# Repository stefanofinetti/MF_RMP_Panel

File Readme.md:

# Radio Management Panel (RMP)

An Airbus A319/320/321 Radio Management Panel for MobiFlight: a 3D-printed
front panel, keys and case, four boards, and two 6-digit frequency displays.
It runs on the **stock MobiFlight Mega firmware**: no custom firmware to
build or flash.

## V5 in short

V5 replaces the earlier version of this repository, a single board with
OLED displays and its own firmware. It is a new design:

* **four boards** instead of one: the logic, the keys and display drivers,
  the lighting, and a carrier for each frequency display;
* **7-segment displays** driven by two MAX7219, which MobiFlight drives
  natively as one LED module;
* **stock firmware**, MobiFlight Mega, core 3.1.4;
* the printed parts are drawn in **FreeCAD 1.1**.

**Status (October 2026):** the unit is built and in use. The boards in this
repository are the built ones, with one correction on the MainPanel (see
[Known issues](#known-issues)). All four are in KiCad 10, with ERC, DRC and
schematic parity clean. The printed parts are being reorganised.

## What is in the repository

| Folder | What it holds |
|---|---|
| [`BoardPanel/`](BoardPanel/README.md) | The logic board: ATmega2560, CH340G USB, 12 V and 5 V supply |
| [`MainPanel/`](MainPanel/README.md) | The keys, the two MAX7219, and the connectors to every other board |
| [`LedsPanel/`](LedsPanel/README.md) | The backlight and the thirteen key lights |
| [`7Segments/`](7Segments/README.md) | The carrier of one frequency display. Two are needed |
| `Libraries/` | The parts shared by the four boards: `RMP.kicad_sym`, `RMP.pretty` and the vendor 3D models in `3dmodels/` |
| `SF_RMP/` | `SF RMP.mfmc`, the MobiFlight board config |
| `3D FIles/` | The FreeCAD sources (`RMP_Panel.FCStd` is the whole assembly), the STL files, the B612 fonts of the legends. Being reorganised |

## The boards

```
 12 V jack ─► BoardPanel ─┬─ J4 ribbon ─► MainPanel J2 ─► J1 ─► LedsPanel (plugged in)
 USB-B     ─►             ├─ J5 ribbon ─► MainPanel J3   keys, encoders, ON/OFF
                          └─ J3 ribbon ─► MainPanel J9 ─┬─ J7 ribbon ─► 7Segments ACTIVE
                                                        └─ J8 ribbon ─► 7Segments STBY
```

| Board | PCB (mm) | What is on it |
|---|---|---|
| [BoardPanel](BoardPanel/README.md) | 110 × 55 | ATmega2560, CH340G, USB-B, 12 V jack, P78A05 5 V module, ISP header |
| [MainPanel](MainPanel/README.md) | 122 × 80 | 13 keys, 2 × MAX7219, encoder and switch connectors |
| [LedsPanel](LedsPanel/README.md) | 122 × 80 | 69 backlight LEDs with their PWM switch, 13 key lights |
| [7Segments](7Segments/README.md) × 2 | 51 × 20 | Two 3-digit common-cathode displays, MHz and kHz |

All four are two-layer, 1.6 mm boards, sized for hand soldering, with
values, polarity and pin 1 on the silkscreen.

## Building one

1. **Print** the panel, keys, case and supports from `3D FIles/`.
2. **Order the boards.** Run the Fabrication Toolkit plugin in each KiCad
   project for the Gerbers, BOM and positions. Order the 7Segments twice.
3. **Assemble** them. The board readmes list what to watch for.
4. **Cable them** as in the diagram above: straight ribbons, pin 1 to
   pin 1. The LedsPanel plugs straight into the MainPanel's J1.
5. **Burn the bootloader** once through the ISP header J2 of the BoardPanel,
   with JP1 on 2–3; then put JP1 back on 1–2. See the
   [BoardPanel readme](BoardPanel/README.md#burning-the-bootloader).
6. **Flash the MobiFlight Mega firmware** from the MobiFlight Connector,
   then load `SF_RMP/SF RMP.mfmc` and upload it to the board.
7. **Bind** the keys, lights, displays and encoders in your MobiFlight
   project.

The BoardPanel's logic runs from USB; the 12 V adapter feeds the backlight,
the displays and the fan.

## MobiFlight

Stock **MobiFlight Mega** firmware, module name `SF RMP`. The config in
`SF_RMP/SF RMP.mfmc` holds:

| Device | Type | Pins |
|---|---|---|
| `Display Freq` | LED module, MAX7219, 2 devices | DIN D23, CLK D22, CS D68. Connector 1 = STBY, connector 2 = ACTIVE |
| `Dimmer` | Output, PWM | D6, the backlight |
| `KHZ_Encoder` | Encoder | Left D27, right D25 |
| `MHZ_Encoder` | Encoder | Left D28, right D26 |
| `VHF1_LED` … `SEL_LED` | Outputs | A0–A12 (D54–D66): VHF1, VHF2, VHF3, HF1, HF2, AM, NAV, VOR, ILS, MLS, ADF, BFO, SEL |

| Key | Pin | Key | Pin | Key | Pin |
|---|---|---|---|---|---|
| XFER | D29 | HF2 | D36 | MLS | D31 |
| VHF1 | D39 | AM | D35 | ADF | D30 |
| VHF2 | D15 | NAV | D34 | BFO | D40 |
| VHF3 | D14 | VOR | D33 | ON/OFF | D41 |
| HF1 | D37 | ILS | D32 | | |

Each MAX7219 drives six digits; the decimal point after the MHz is set in
the project row of each display.

## Known issues

* **The first MainPanel had the two MAX7219 side by side instead of in a
  chain.** The files here are corrected. A board built from the first files
  needs two wires, described in the
  [MainPanel readme](MainPanel/README.md#boards-built-before-this-revision).
* **Two STL files are empty:** the white parts of the VHF1 and VHF3 keys.
  They will be re-exported from FreeCAD with the reorganisation of the
  printed parts.

## Software

* [KiCad](https://www.kicad.org/) 10. The files are saved by KiCad 10 and
  do not open in older versions
* [FreeCAD](https://www.freecad.org/) 1.1, to change the printed parts
* [MobiFlight](https://www.mobiflight.com/)

```bash
git clone https://github.com/stefanofinetti/MF_RMP_Panel.git
```

## License

This code and all the items are released under the GPLv3.0 license. Feel free
to use them as you wish, as long as you redistribute the source code.
A mention would be nice, though, if you use this work: I invested a good
many hours in it, just for the amazing MobiFlight community.

## Acknowledgements

This project couldn't have seen the light without the excellent work, and
kind support, of [GaGagu](https://github.com/gagagu) and
[ElRal](https://github.com/elral). Their work is amazing, so please have a
look at their repositories.

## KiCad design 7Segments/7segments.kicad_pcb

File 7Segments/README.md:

# RMP 7Segments

The carrier of one frequency display: two 3-digit 7-segment displays,
MHz and kHz, side by side. **Two are needed**, one for ACTIVE and one for
STBY. Each sits in its printed display case and reaches the MainPanel
through a 16-pin ribbon.

* **PCB:** 51 × 20 mm, 2 layers, 1.6 mm, GND poured on both sides.
* **Fixing:** six M2 holes.
* **Parts:** 5: four socket strips for the displays on the top, one header
  on the bottom.
* **Status:** built and in use. ERC and schematic parity are clean; DRC
  reports only silkscreen clipped by the solder mask around J5.

| Top: the display sockets | Bottom: J5 |
|---|---|
|  |  |

Rendered by KiCad from the board file. The bottom is seen from below, so it
is mirrored against the top.

## Connectors

| Ref | What | Notes |
|---|---|---|
| J1 / J2 | Socket strips 1 × 6 / 1 × 5 | kHz display, upper and lower row of pins |
| J3 / J4 | Socket strips 1 × 6 / 1 × 5 | MHz display, upper and lower row of pins |
| J5 | Shrouded IDC header 2 × 8, on the bottom | To MainPanel J7 (ACTIVE) or J8 (STBY), pin 1 to pin 1 |

**J5:** odd pins are the segments, 1 A, 3 B, 5 C, 7 D, 9 E, 11 F, 13 G,
15 the decimal point; even pins are the digits, 2 / 4 / 6 kHz 3 / 2 / 1,
8 / 10 / 12 MHz 3 / 2 / 1; 14 and 16 GND.

The displays must be **common cathode**: the MAX7219 sinks the digits and
drives the segments. The decimal point is wired on both displays; which digit
shows it is set in the MobiFlight project.

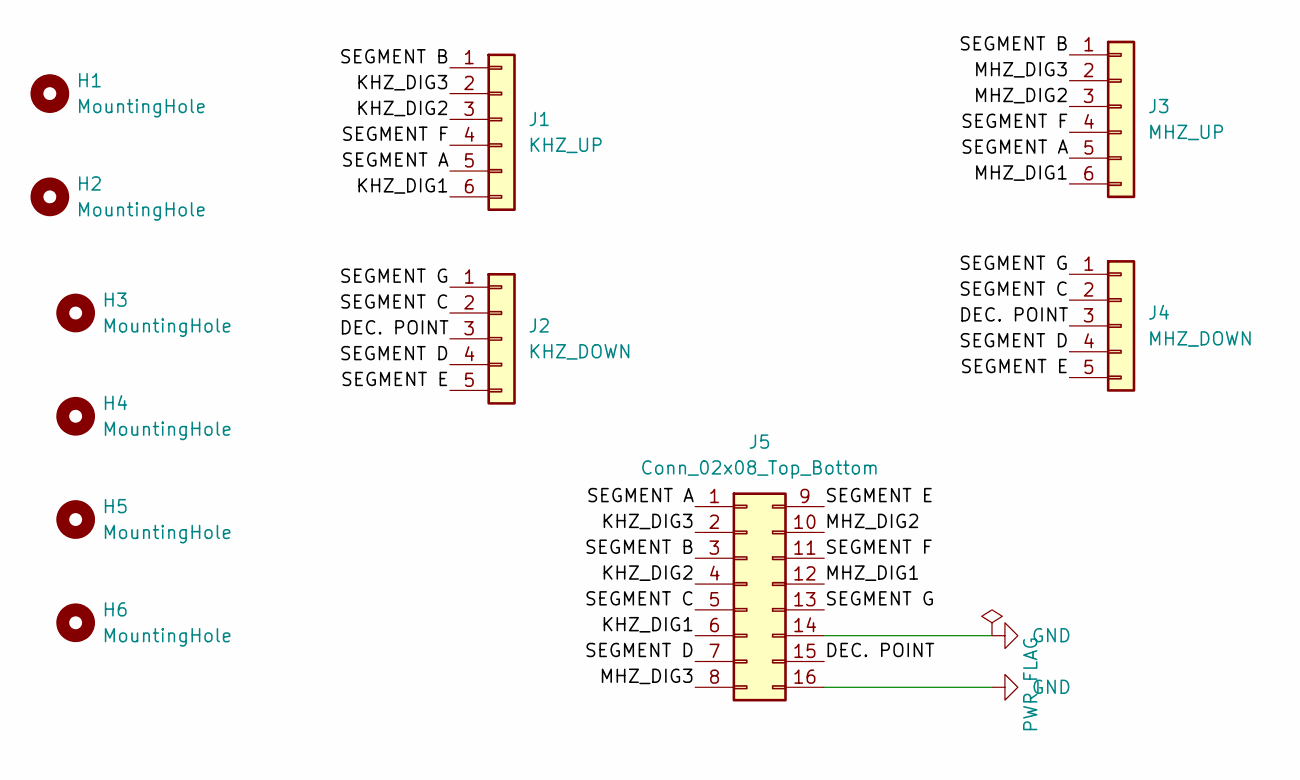
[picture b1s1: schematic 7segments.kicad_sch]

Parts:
H1, H2, H3, H4, H5, H6: MountingHole; MountingHole_2.2mm_M2
J1: KHZ_UP; PinSocket_1x06_P2.54mm_Vertical
J2: KHZ_DOWN; PinSocket_1x05_P2.54mm_Vertical
J3: MHZ_UP; PinSocket_1x06_P2.54mm_Vertical
J4: MHZ_DOWN; PinSocket_1x05_P2.54mm_Vertical
J5: Conn_02x08_Top_Bottom; IDC-Header_2x08_P2.54mm_Vertical

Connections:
/DEC. POINT: J2.3, J4.3, J5.15
/KHZ_DIG1: J1.6, J5.6
/KHZ_DIG2: J1.3, J5.4
/KHZ_DIG3: J1.2, J5.2
/MHZ_DIG1: J3.6, J5.12
/MHZ_DIG2: J3.3, J5.10
/MHZ_DIG3: J3.2, J5.8
/SEGMENT A: J1.5, J3.5, J5.1
/SEGMENT B: J1.1, J3.1, J5.3
/SEGMENT C: J2.2, J4.2, J5.5
/SEGMENT D: J2.4, J4.4, J5.7
/SEGMENT E: J2.5, J4.5, J5.9
/SEGMENT F: J1.4, J3.4, J5.11
/SEGMENT G: J2.1, J4.1, J5.13
GND: J5.14, J5.16

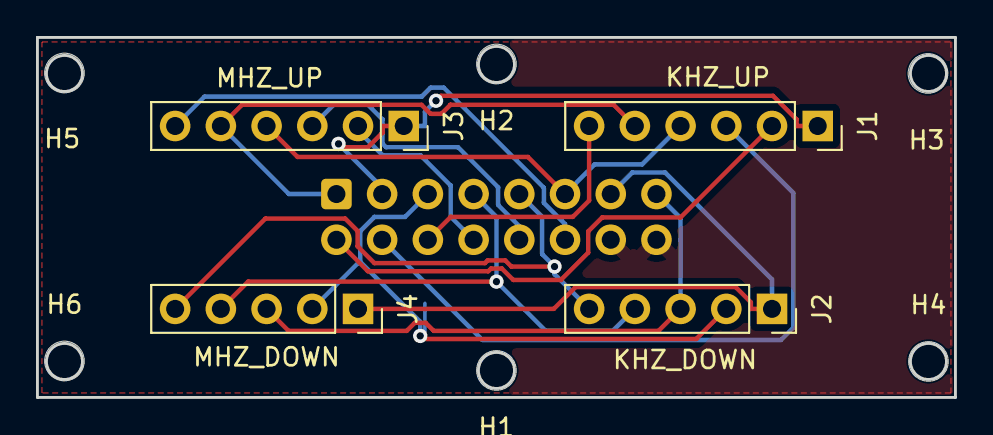
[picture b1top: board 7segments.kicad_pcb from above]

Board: 2 copper layers, 51.0 x 20.0 mm, 11 parts (1 on the bottom side), 15 nets.

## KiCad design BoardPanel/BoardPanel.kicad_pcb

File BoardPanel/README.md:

# RMP BoardPanel

The logic board of the RMP: the microcontroller, USB and power. It stands
upright on the printed support at the back of the case and reaches the
MainPanel through three ribbons.

* **PCB:** 110 × 55 mm, 2 layers, 1.6 mm, GND poured on both sides.
* **Fixing:** six M2 holes.
* **Parts:** 44, all on the top.
* **Status:** built and in use. ERC, DRC and schematic parity are clean.

| Top | Bottom |
|---|---|
|  |  |

Rendered by KiCad from the board file. The bottom is seen from below, so it
is mirrored against the top.

## What is on it

* **Microcontroller:** ATmega2560 (U1) with a 16 MHz crystal, and a CH340G
  (U3, 12 MHz crystal) for USB. MobiFlight sees it as a Mega.
* **Power:**
  * 12 V from the barrel jack J1, through D2, is the `+12V` rail: the
    backlight (J4) and the fan (J6).
  * From `+12V`, through D1, a P78A05 switching module (U2) makes the 5 V
    for the two MAX7219 only (J3).
  * The ATmega and the CH340G run from USB, through D3 and JP1. The
    displays and the backlight need the 12 V; the logic does not.

## Connectors and settings

| Ref | What | Notes |
|---|---|---|
| J1 | 12 V in, 5.5 × 2.1 barrel jack | Pin 1 `+`, through D2 |
| P1 | USB-B | To the computer |
| J2 | ISP header, 1 × 6 | 1 VCC, 2 RESET, 3 MISO, 4 MOSI, 5 SCK, 6 GND |
| JP1 | Power selector | 1–2: MCU from USB (normal use). 2–3: MCU from J2's VCC only, to burn the bootloader |
| J3 | Displays, IDC 2 × 3 | To MainPanel J9 |
| J4 | LEDs and backlight, IDC 2 × 9 | To MainPanel J2 |
| J5 | Buttons and encoders, IDC 2 × 11 | To MainPanel J3 |
| J6 | Cooling fan, 2 pins | `+12V` and GND, for a 12 V fan |
| S1 | Reset | |

Every ribbon is straight, pin 1 to pin 1.

**J3, displays:** 1 `+5V`, 2 GND, 3 D67 (marked `AL`, no longer used, see
the MainPanel), 4 CLK (D22), 5 DIN (D23), 6 LOAD (D68).

**J4, LEDs and backlight:** 1 `+12V`, 2 GND, 3 backlight PWM (D6), 4 GND,
5–17 the thirteen key LEDs (A0–A12, in the order VHF1, VHF2, VHF3, HF1,
HF2, AM, NAV, VOR, ILS, MLS, ADF, BFO, SEL), 18 GND.

**J5, buttons and encoders:** see the pin map in the
[main readme](../Readme.md#mobiflight).

## Burning the bootloader

A new ATmega2560 is blank. Put JP1 on 2–3, so the programmer powers the
MCU alone through J2, and burn the Arduino Mega bootloader once. Then put
JP1 back on 1–2. From then on the board is flashed over USB like a Mega.

## Assembly notes

* Everything is sized for hand soldering: 1206 passives, 5 × 3.2 mm
  crystals.
* Values, polarity and pin 1 are on the silkscreen.

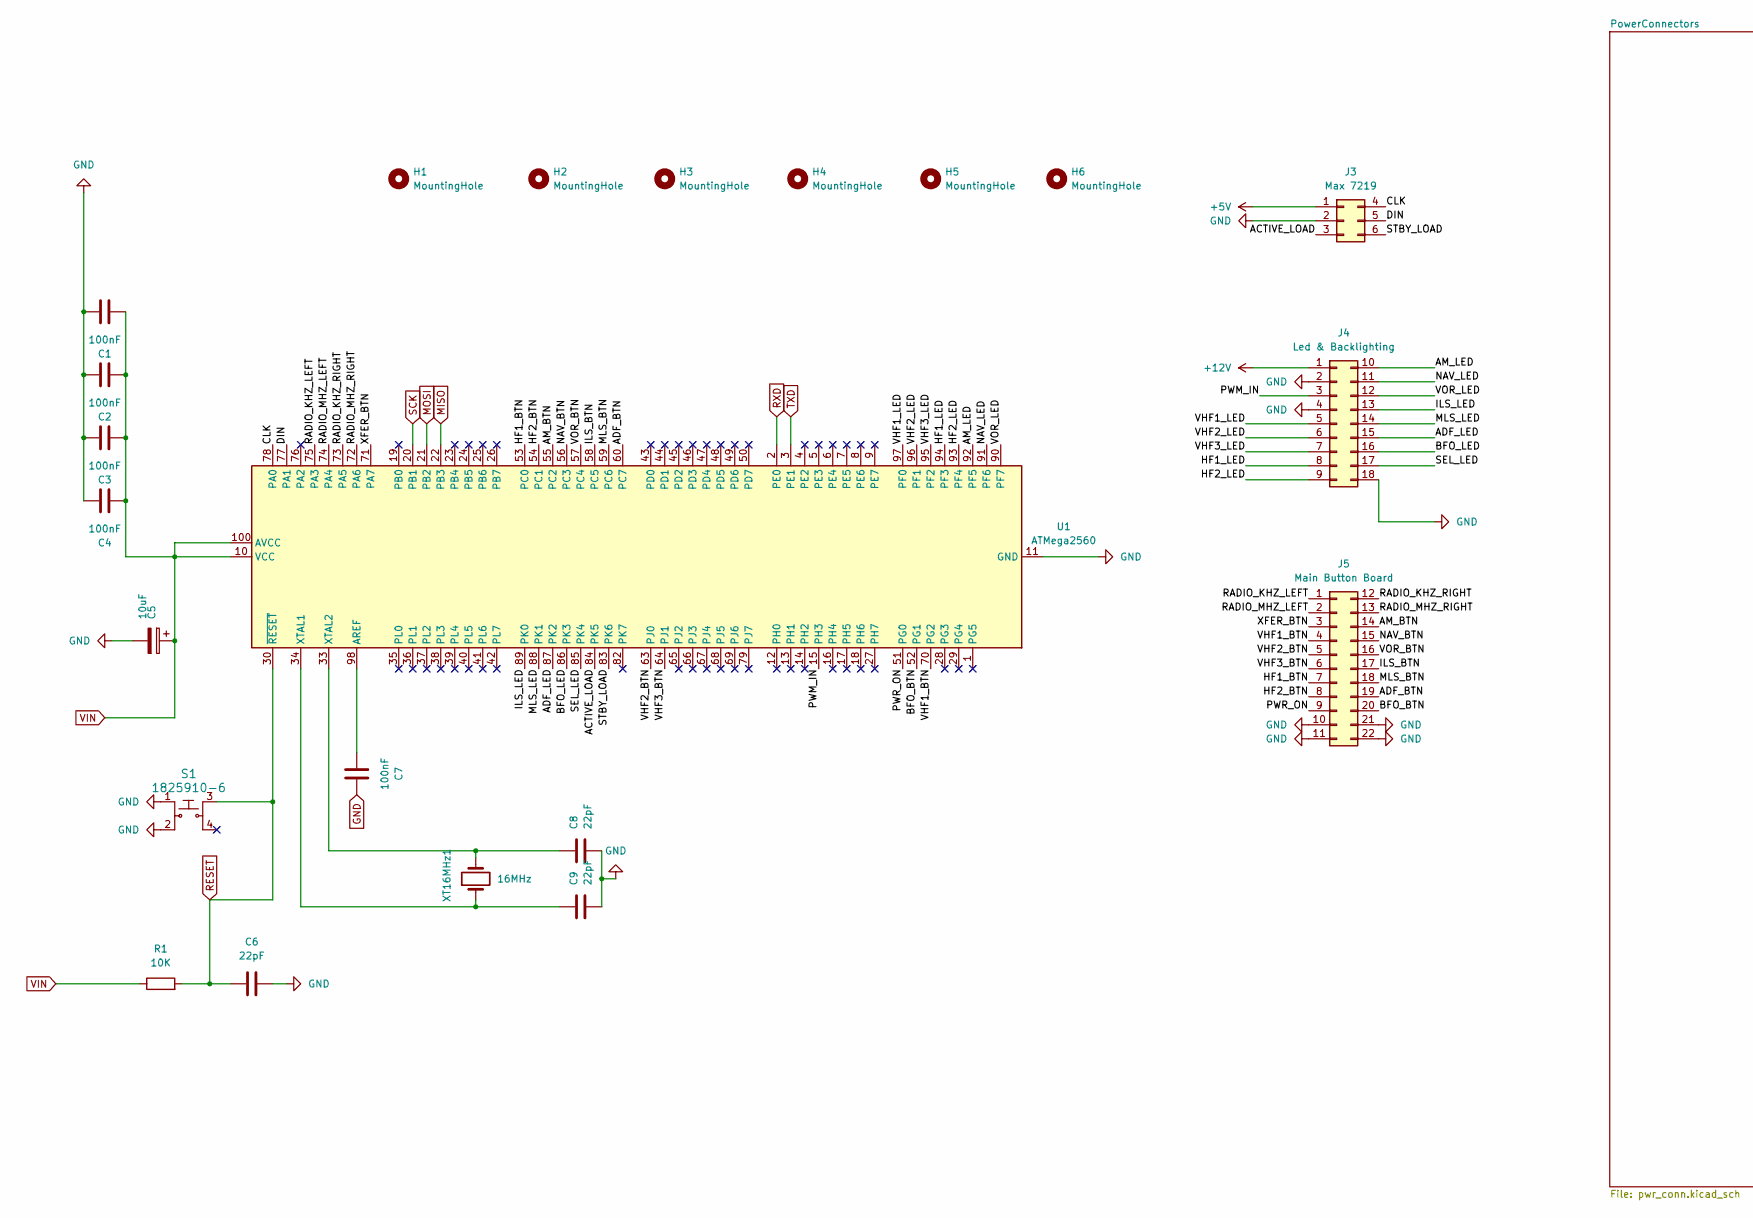
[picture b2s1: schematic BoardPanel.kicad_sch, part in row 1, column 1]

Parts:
C1, C2, C3, C4, C7: 100nF; C_1206_3216Metric_Pad1.33x1.80mm_HandSolder
C5: 10uF; C_Elec_4x5.4
C6, C8, C9: 22pF; C_1206_3216Metric_Pad1.33x1.80mm_HandSolder
H1, H2, H3, H4, H5, H6: MountingHole; MountingHole_2.2mm_M2_DIN965
J3: Max 7219; IDC-Header_2x03_P2.54mm_Vertical
J4: Led & Backlighting; IDC-Header_2x09_P2.54mm_Vertical
J5: Main Button Board; IDC-Header_2x11_P2.54mm_Vertical
R1: 10K; R_1206_3216Metric_Pad1.30x1.75mm_HandSolder
S1: 1825910-6; Switch_Tactile_THT_6x6mm_MJTP1230; MPN 1825910-6; Digi-Key_PN 450-1650-ND
U1: ATMega2560; TQFP100-0.5-14X14MM
XT16MHz1: 16MHz; Crystal_SMD_5032-2Pin_5.0x3.2mm_HandSoldering

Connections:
+5V: J3.1; also elsewhere on the board
+12V: J4.1; also elsewhere on the board
/ACTIVE_LOAD: J3.3, U1.84 (PK5)
/ADF_BTN: J5.19, U1.60 (PC7)
/ADF_LED: J4.15, U1.87 (PK2)
/AM_BTN: J5.14, U1.55 (PC2)
/AM_LED: J4.10, U1.92 (PF5)
/BFO_BTN: J5.20, U1.52 (PG1)
/BFO_LED: J4.16, U1.86 (PK3)
/CLK: J3.4, U1.78 (PA0)
/DIN: J3.5, U1.77 (PA1)
/HF1_BTN: J5.7, U1.53 (PC0)
/HF1_LED: J4.8, U1.94 (PF3)
/HF2_BTN: J5.8, U1.54 (PC1)
/HF2_LED: J4.9, U1.93 (PF4)
/ILS_BTN: J5.17, U1.58 (PC5)
/ILS_LED: J4.13, U1.89 (PK0)
/MLS_BTN: J5.18, U1.59 (PC6)
/MLS_LED: J4.14, U1.88 (PK1)
/NAV_BTN: J5.15, U1.56 (PC3)
/NAV_LED: J4.11, U1.91 (PF6)
/PWM_IN: J4.3, U1.15 (PH3)
/PWR_ON: J5.9, U1.51 (PG0)
/RADIO_KHZ_LEFT: J5.1, U1.75 (PA3)
/RADIO_KHZ_RIGHT: J5.12, U1.73 (PA5)
/RADIO_MHZ_LEFT: J5.2, U1.74 (PA4)
/RADIO_MHZ_RIGHT: J5.13, U1.72 (PA6)
/SEL_LED: J4.17, U1.85 (PK4)
/STBY_LOAD: J3.6, U1.83 (PK6)
/VHF1_BTN: J5.4, U1.70 (PG2)
/VHF1_LED: J4.5, U1.97 (PF0)
/VHF2_BTN: J5.5, U1.63 (PJ0)
/VHF2_LED: J4.6, U1.96 (PF1)
/VHF3_BTN: J5.6, U1.64 (PJ1)
/VHF3_LED: J4.7, U1.95 (PF2)
/VOR_BTN: J5.16, U1.57 (PC4)
/VOR_LED: J4.12, U1.90 (PF7)
/XFER_BTN: J5.3, U1.71 (PA7)
GND: C1.2, C2.2, C3.2, C4.2, C5.2, C6.2, C7.2, C8.2, C9.2, J3.2, J4.2, J4.4, J4.18, J5.10, J5.11, J5.21, J5.22, S1.1, S1.2, U1.11 (GND), U1.32 (GND), U1.62 (GND), U1.81 (GND), U1.99 (GND); also elsewhere on the board
MISO: U1.22 (PB3); also elsewhere on the board
MOSI: U1.21 (PB2); also elsewhere on the board
unnamed: C7.1, U1.98 (AREF)
unnamed: C9.1, U1.34 (XTAL1), XT16MHz1.1
unnamed: C8.1, U1.33 (XTAL2), XT16MHz1.2
RESET: C6.1, R1.2, S1.3, U1.30 (~RESET); also elsewhere on the board
RXD: U1.2 (PE0); also elsewhere on the board
SCK: U1.20 (PB1); also elsewhere on the board
TXD: U1.3 (PE1); also elsewhere on the board
VIN: C1.1, C2.1, C3.1, C4.1, C5.1, R1.1, U1.10 (VCC), U1.31 (VCC), U1.61 (VCC), U1.80 (VCC), U1.100 (AVCC); also elsewhere on the board

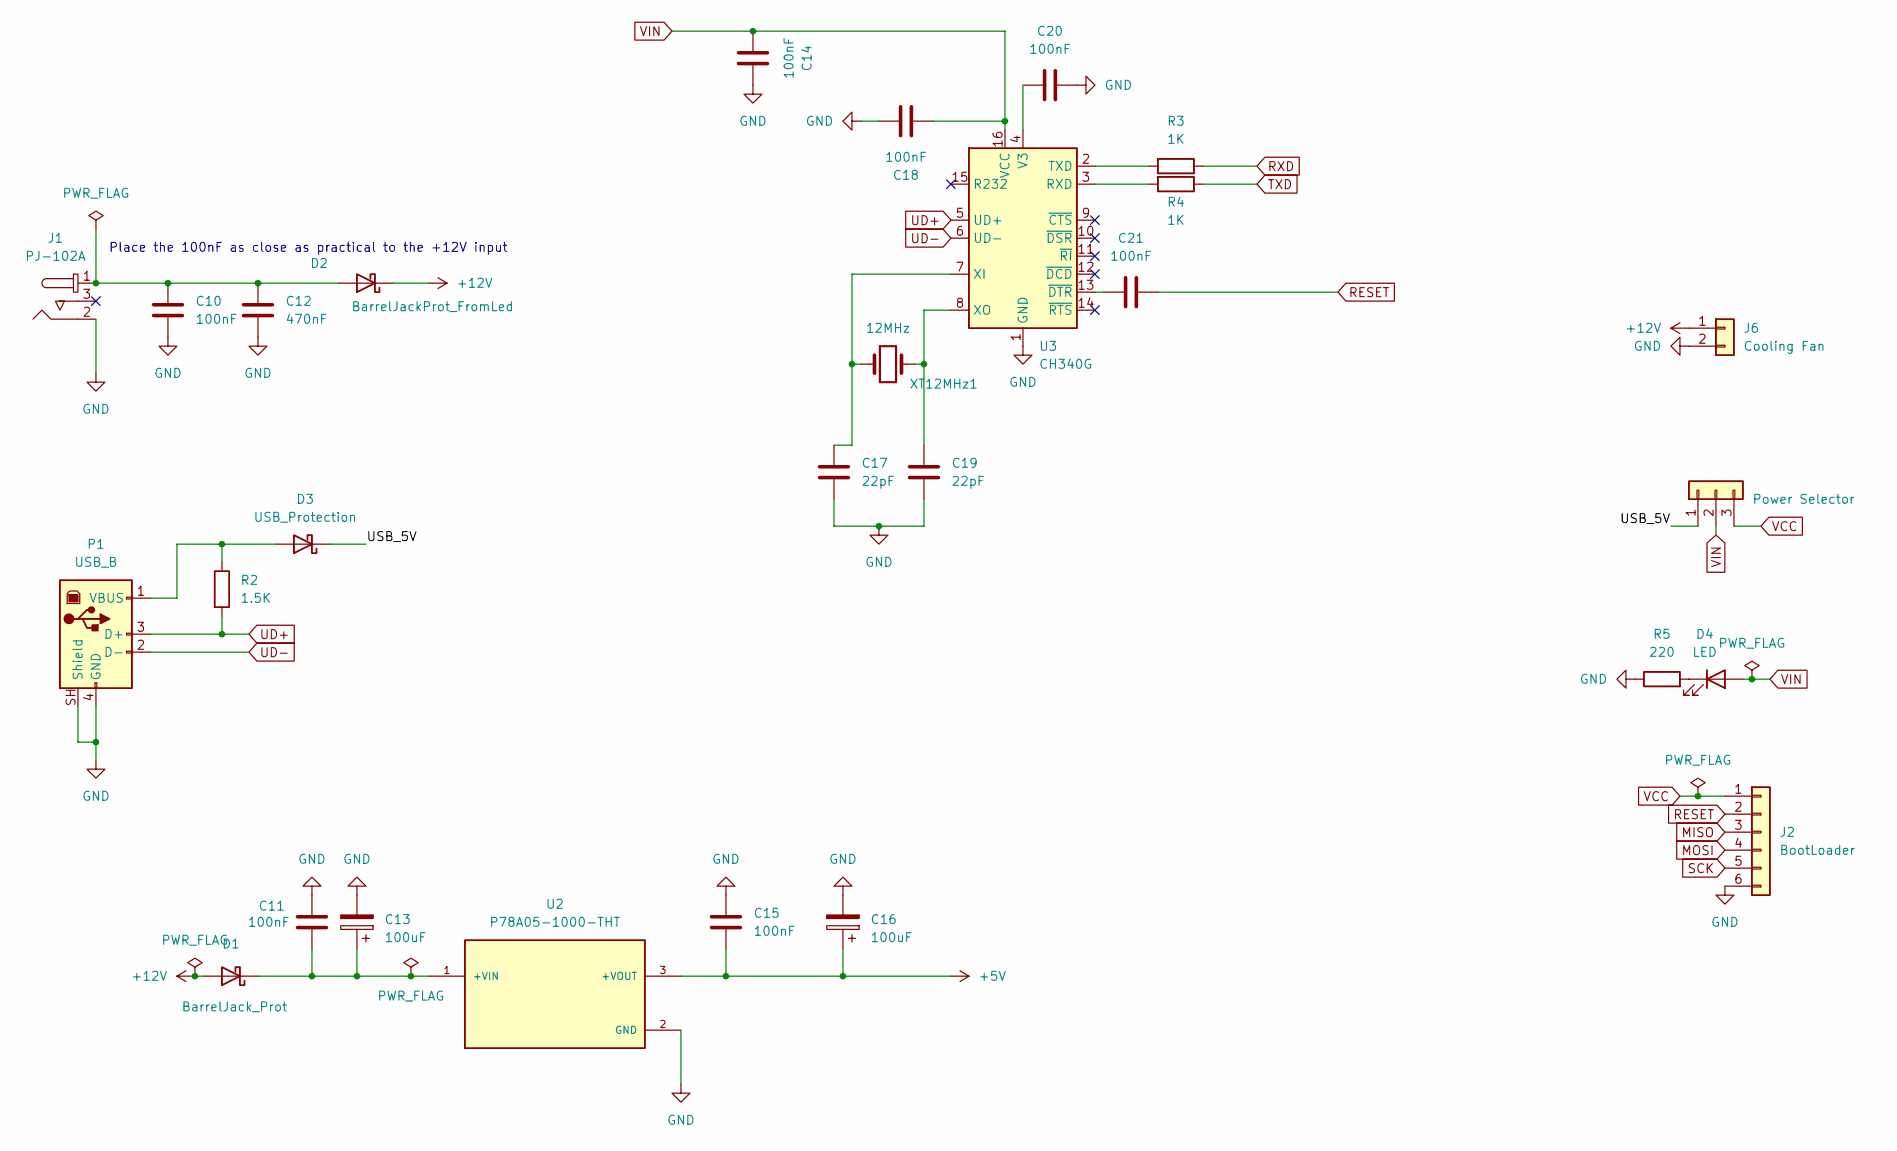
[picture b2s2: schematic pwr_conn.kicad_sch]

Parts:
C10, C11, C14, C15, C18, C20, C21: 100nF; C_1206_3216Metric_Pad1.33x1.80mm_HandSolder
C12: 470nF; C_1206_3216Metric_Pad1.33x1.80mm_HandSolder
C13, C16: 100uF; C_Elec_6.3x7.7
C17, C19: 22pF; C_1206_3216Metric_Pad1.33x1.80mm_HandSolder
D1: BarrelJack_Prot; D_SMA
D2: BarrelJackProt_FromLed; D_SMA
D3: USB_Protection; D_SMA
D4: LED; LED_1206_3216Metric_Pad1.42x1.75mm_HandSolder
J1: PJ-102A; Barrel_Jack_5.5mmODx2.1mmID_PJ-102A; MPN PJ-102A; Digi-Key_PN CP-102A-ND
J2: BootLoader; PinHeader_1x06_P2.54mm_Vertical
J6: Cooling Fan; PinHeader_1x02_P2.54mm_Vertical
JP1: Power Selector; PinHeader_1x03_P2.54mm_Vertical
P1: USB_B; USB_B_OST_USB-B1HSxx_Horizontal
R2: 1.5K; R_1206_3216Metric_Pad1.30x1.75mm_HandSolder
R3, R4: 1K; R_1206_3216Metric_Pad1.30x1.75mm_HandSolder
R5: 220; R_1206_3216Metric_Pad1.30x1.75mm_HandSolder
U2: P78A05-1000-THT; CONV_P78A05-1000; PARTREV 1.0
U3: CH340G; SOIC-16_3.9x9.9mm_P1.27mm
XT12MHz1: 12MHz; Crystal_SMD_5032-2Pin_5.0x3.2mm_HandSoldering

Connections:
+5V: C15.2, C16.1, U2.3 (+VOUT); also elsewhere on the board
+12V: D1.2 (A), D2.1 (K), J6.1; also elsewhere on the board
/PowerConnectors/USB_5V: D3.1 (K), JP1.1
GND: C10.2, C11.1, C12.2, C13.2, C14.2, C15.1, C16.2, C17.1, C18.2, C19.1, C20.2, J1.2, J2.6, J6.2, P1.4 (GND), P1.SH (Shield), R5.1, U2.2 (GND), U3.1 (GND); also elsewhere on the board
MISO: J2.3; also elsewhere on the board
MOSI: J2.4; also elsewhere on the board
unnamed: C11.2, C13.1, D1.1 (K), U2.1 (+VIN)
unnamed: C10.1, C12.1, D2.2 (A), J1.1
unnamed: D3.2 (A), P1.1 (VBUS), R2.1
unnamed: D4.1 (K), R5.2
unnamed: R4.2, U3.3 (RXD)
unnamed: R3.2, U3.2 (TXD)
unnamed: C20.1, U3.4 (V3)
unnamed: C17.2, U3.7 (XI), XT12MHz1.1
unnamed: C19.2, U3.8 (XO), XT12MHz1.2
unnamed: C21.1, U3.13 (~DTR)
RESET: C21.2, J2.2; also elsewhere on the board
RXD: R3.1; also elsewhere on the board
SCK: J2.5; also elsewhere on the board
TXD: R4.1; also elsewhere on the board
UD+: P1.3 (D+), R2.2, U3.5 (UD+)
UD-: P1.2 (D-), U3.6 (UD-)
VCC: J2.1, JP1.3
VIN: C14.1, C18.1, D4.2 (A), JP1.2, U3.16 (VCC); also elsewhere on the board

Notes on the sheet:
Place the 100nF as close as practical to the +12V input

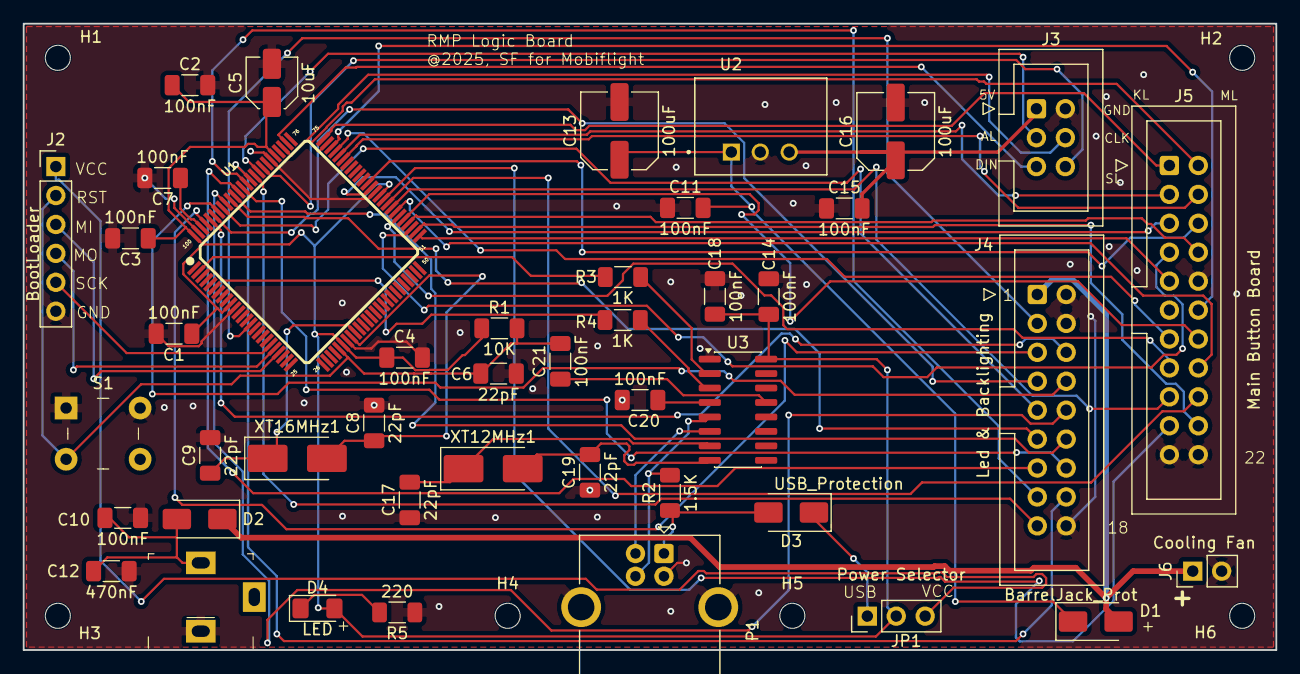
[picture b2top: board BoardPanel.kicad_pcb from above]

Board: 2 copper layers, 110.0 x 55.0 mm, 50 parts (0 on the bottom side), 63 nets.

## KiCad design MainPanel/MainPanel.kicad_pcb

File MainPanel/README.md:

# RMP MainPanel

The board behind the front panel: the thirteen keys, the two MAX7219 that
drive the frequency displays, and the connectors for the encoders, the
ON/OFF switch, the LedsPanel and the two display boards. It reaches the
BoardPanel through three ribbons.

* **PCB:** 122 × 80 mm, 2 layers, 1.6 mm, GND poured on both sides.
* **Fixing:** five 2.5 mm holes.
* **Parts:** 30. On the top: the keys, J1 for the LedsPanel and the two
  encoder sockets. On the bottom: the two MAX7219 with their passives, and
  the headers to the BoardPanel, the display boards and the ON/OFF switch.
* **Status:** the display chain is corrected in this revision (see below)
  and rerouted. ERC, DRC and schematic parity are clean. The corrected
  board has not been ordered yet.

| Top: the keys | Bottom: drivers and connectors |
|---|---|
|  |  |

Rendered by KiCad from the board file. The bottom is seen from below, so it
is mirrored against the top.

## Connectors

| Ref | What | Goes to |
|---|---|---|
| J1 | Socket 2 × 9 | The LedsPanel's J1 plugs in here. Same pins as J2 |
| J2 | Header 2 × 9 | BoardPanel J4: backlight, PWM, the thirteen key LEDs |
| J3 | Header 2 × 11 | BoardPanel J5: keys, encoders, ON/OFF |
| J9 | Header 2 × 3 | BoardPanel J3: the display bus |
| J7 | Header 2 × 8 | ACTIVE display board, its J5 |
| J8 | Header 2 × 8 | STBY display board, its J5 |
| J5 | Socket 1 × 3 | kHz encoder: 1 `RADIO_KHZ_LEFT` (D25), 2 GND, 3 `RADIO_KHZ_RIGHT` (D27) |
| J6 | Socket 2 × 3 | MHz encoder: 2 `RADIO_MHZ_LEFT` (D26), 4 GND, 6 `RADIO_MHZ_RIGHT` (D28). Pins 1, 3, 5 are not connected |
| J4 | Header 1 × 2 | ON/OFF switch: 1 to D41, 2 GND |

Every connection is pin 1 to pin 1. The pinouts of J2, J3 and J9 are in
the [BoardPanel readme](../BoardPanel/README.md#connectors-and-settings).

## The keys

S1–S13, 6 × 6 mm tactile switches, each between its input and GND. The
MCU's internal pull-ups hold the inputs high.

| S1 | S2 | S3 | S4 | S5 | S6 | S7 | S8 | S9 | S10 | S11 | S12 | S13 |
|---|---|---|---|---|---|---|---|---|---|---|---|---|
| VHF1 | VHF2 | VHF3 | XFER | HF1 | HF2 | AM | NAV | VOR | ILS | MLS | ADF | BFO |

## The displays

Two MAX7219 in one chain, as MobiFlight expects for one LED module of two
devices:

```
D23 (DIN) ─► U2 STBY ─► DOUT ─► U1 ACTIVE
D22 (CLK) ─► U1 and U2
D68 (LOAD) ─► U1 and U2
```

U2 is the first device in the chain, so in MobiFlight connector 1 is the
standby frequency and connector 2 the active one. Each chip drives six
digits, three for MHz and three for kHz, through J7 / J8 to its display
board. R1 and R2 (22 kΩ) on `ISET` set the segment current; C1–C4 decouple
the two chips.

### Boards built before this revision

The first MainPanel had the two chips side by side on D23, with a LOAD
each (D67 for the Active, D68 for the Standby), and nothing on either
DOUT. That board works only with two hand-soldered wires, on the bottom:

1. pin 12 (LOAD) of U1 to pin 12 of U2;
2. pin 24 (DOUT) of U2 to pin 1 (DIN) of U1.

In the production files of that board, U1's pin 1 is also tied to D23 by
copper, which with the second wire gives it two drivers. If the Active
display shows the odd wrong segment now and then, check with the power off
for continuity between pin 1 of U1 and pin 1 of U2. If there is, cut the
track close to U1 pin 1.

## Assembly notes

* Everything is sized for hand soldering: 1206 passives, SOIC-24W chips.
* Values, polarity and pin 1 are on the silkscreen.

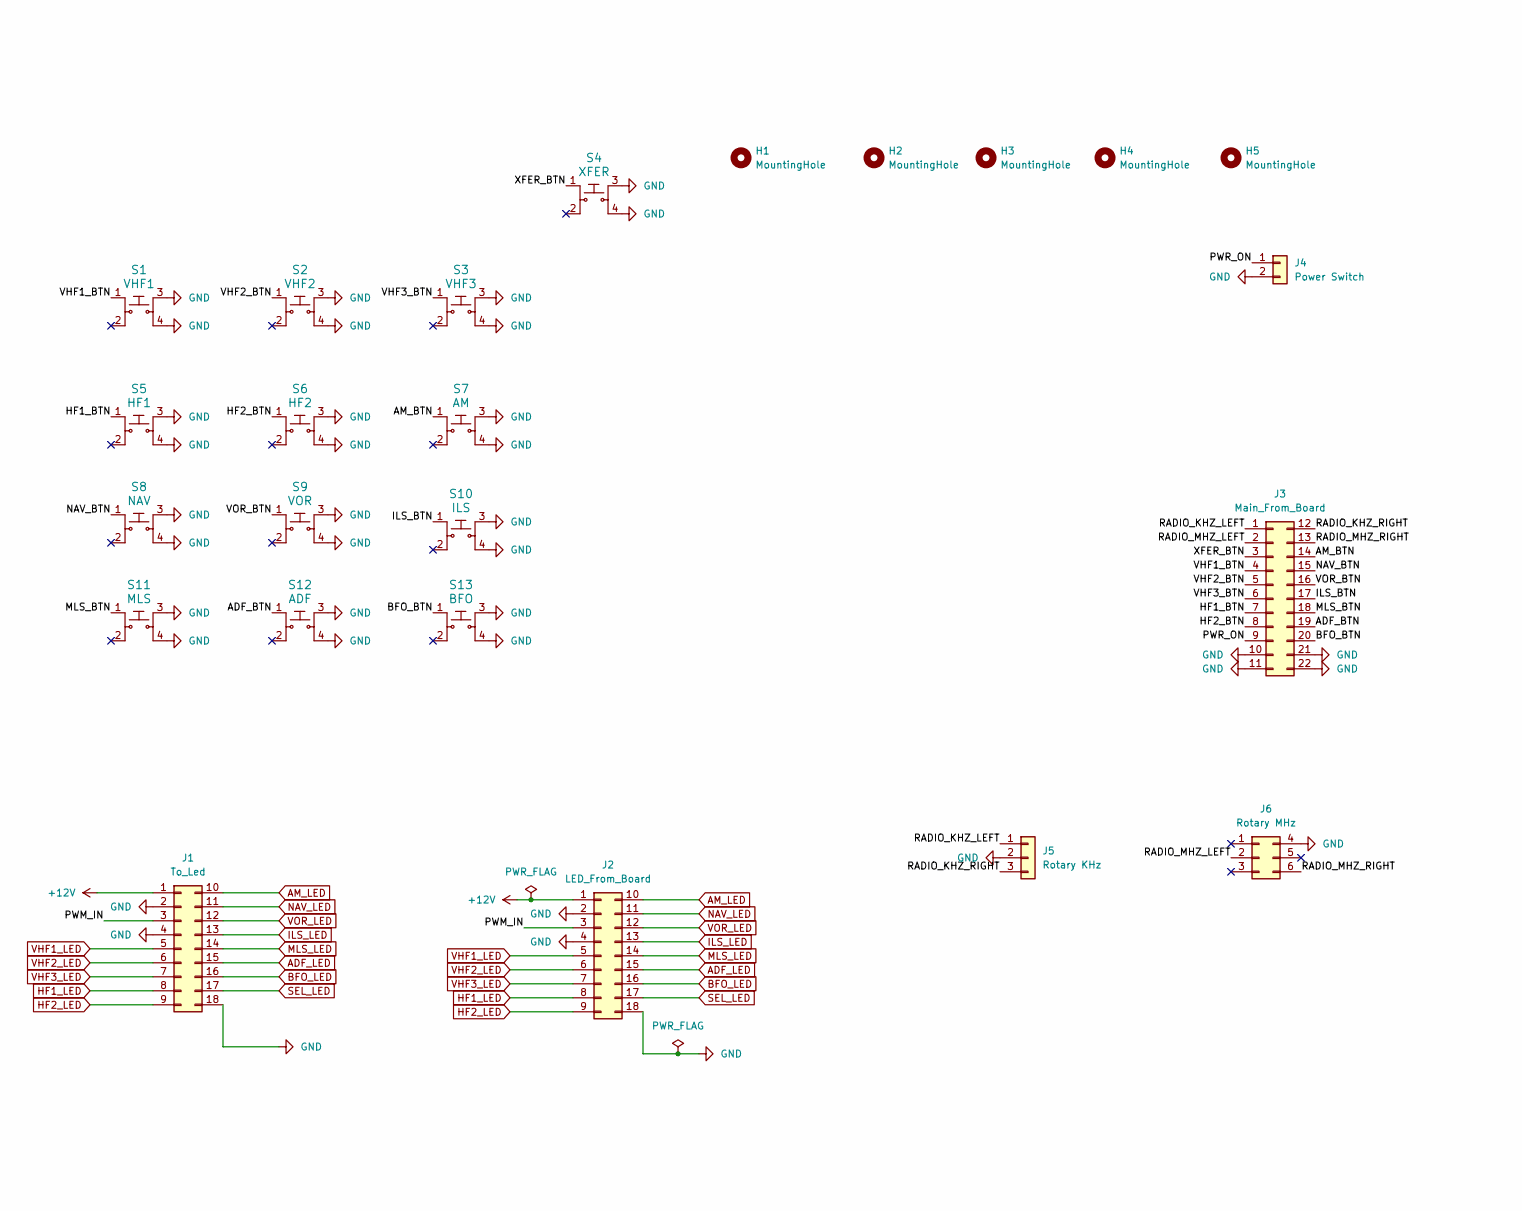
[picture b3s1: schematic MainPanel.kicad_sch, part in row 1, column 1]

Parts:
H1, H2, H3, H4, H5: MountingHole; MountingHole_2.5mm
J1: To_Led; PinSocket_2x09_P2.54mm_Vertical
J2: LED_From_Board; PinHeader_2x09_P2.54mm_Vertical
J3: Main_From_Board; PinHeader_2x11_P2.54mm_Vertical
J4: Power Switch; PinHeader_1x02_P2.54mm_Vertical
J5: Rotary KHz; PinSocket_1x03_P2.54mm_Vertical
J6: Rotary MHz; PinSocket_2x03_P2.54mm_Vertical
S1: VHF1; Switch_Tactile_THT_6x6mm_MJTP1230; MPN MJTP1230; Digi-Key_PN 679-2428-ND
S2: VHF2; Switch_Tactile_THT_6x6mm_MJTP1230; MPN MJTP1230; Digi-Key_PN 679-2428-ND
S3: VHF3; Switch_Tactile_THT_6x6mm_MJTP1230; MPN MJTP1230; Digi-Key_PN 679-2428-ND
S4: XFER; Switch_Tactile_THT_6x6mm_MJTP1230; MPN MJTP1230; Digi-Key_PN 679-2428-ND
S5: HF1; Switch_Tactile_THT_6x6mm_MJTP1230; MPN MJTP1230; Digi-Key_PN 679-2428-ND
S6: HF2; Switch_Tactile_THT_6x6mm_MJTP1230; MPN MJTP1230; Digi-Key_PN 679-2428-ND
S7: AM; Switch_Tactile_THT_6x6mm_MJTP1230; MPN MJTP1230; Digi-Key_PN 679-2428-ND
S8: NAV; Switch_Tactile_THT_6x6mm_MJTP1230; MPN MJTP1230; Digi-Key_PN 679-2428-ND
S9: VOR; Switch_Tactile_THT_6x6mm_MJTP1230; MPN MJTP1230; Digi-Key_PN 679-2428-ND
S10: ILS; Switch_Tactile_THT_6x6mm_MJTP1230; MPN MJTP1230; Digi-Key_PN 679-2428-ND
S11: MLS; Switch_Tactile_THT_6x6mm_MJTP1230; MPN MJTP1230; Digi-Key_PN 679-2428-ND
S12: ADF; Switch_Tactile_THT_6x6mm_MJTP1230; MPN MJTP1230; Digi-Key_PN 679-2428-ND
S13: BFO; Switch_Tactile_THT_6x6mm_MJTP1230; MPN MJTP1230; Digi-Key_PN 679-2428-ND

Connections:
+12V: J1.1, J2.1
/ADF_BTN: J3.19, S12.1
/AM_BTN: J3.14, S7.1
/BFO_BTN: J3.20, S13.1
/HF1_BTN: J3.7, S5.1
/HF2_BTN: J3.8, S6.1
/ILS_BTN: J3.17, S10.1
/MLS_BTN: J3.18, S11.1
/NAV_BTN: J3.15, S8.1
/PWM_IN: J1.3, J2.3
/PWR_ON: J3.9, J4.1
/RADIO_KHZ_LEFT: J3.1, J5.1
/RADIO_KHZ_RIGHT: J3.12, J5.3
/RADIO_MHZ_LEFT: J3.2, J6.2
/RADIO_MHZ_RIGHT: J3.13, J6.6
/VHF1_BTN: J3.4, S1.1
/VHF2_BTN: J3.5, S2.1
/VHF3_BTN: J3.6, S3.1
/VOR_BTN: J3.16, S9.1
/XFER_BTN: J3.3, S4.1
ADF_LED: J1.15, J2.15
AM_LED: J1.10, J2.10
BFO_LED: J1.16, J2.16
GND: J1.2, J1.4, J1.18, J2.2, J2.4, J2.18, J3.10, J3.11, J3.21, J3.22, J4.2, J5.2, J6.4, S1.3, S1.4, S2.3, S2.4, S3.3, S3.4, S4.3, S4.4, S5.3, S5.4, S6.3, S6.4, S7.3, S7.4, S8.3, S8.4, S9.3, S9.4, S10.3, S10.4, S11.3, S11.4, S12.3, S12.4, S13.3, S13.4; also elsewhere on the board
HF1_LED: J1.8, J2.8
HF2_LED: J1.9, J2.9
ILS_LED: J1.13, J2.13
MLS_LED: J1.14, J2.14
NAV_LED: J1.11, J2.11
SEL_LED: J1.17, J2.17
VHF1_LED: J1.5, J2.5
VHF2_LED: J1.6, J2.6
VHF3_LED: J1.7, J2.7
VOR_LED: J1.12, J2.12

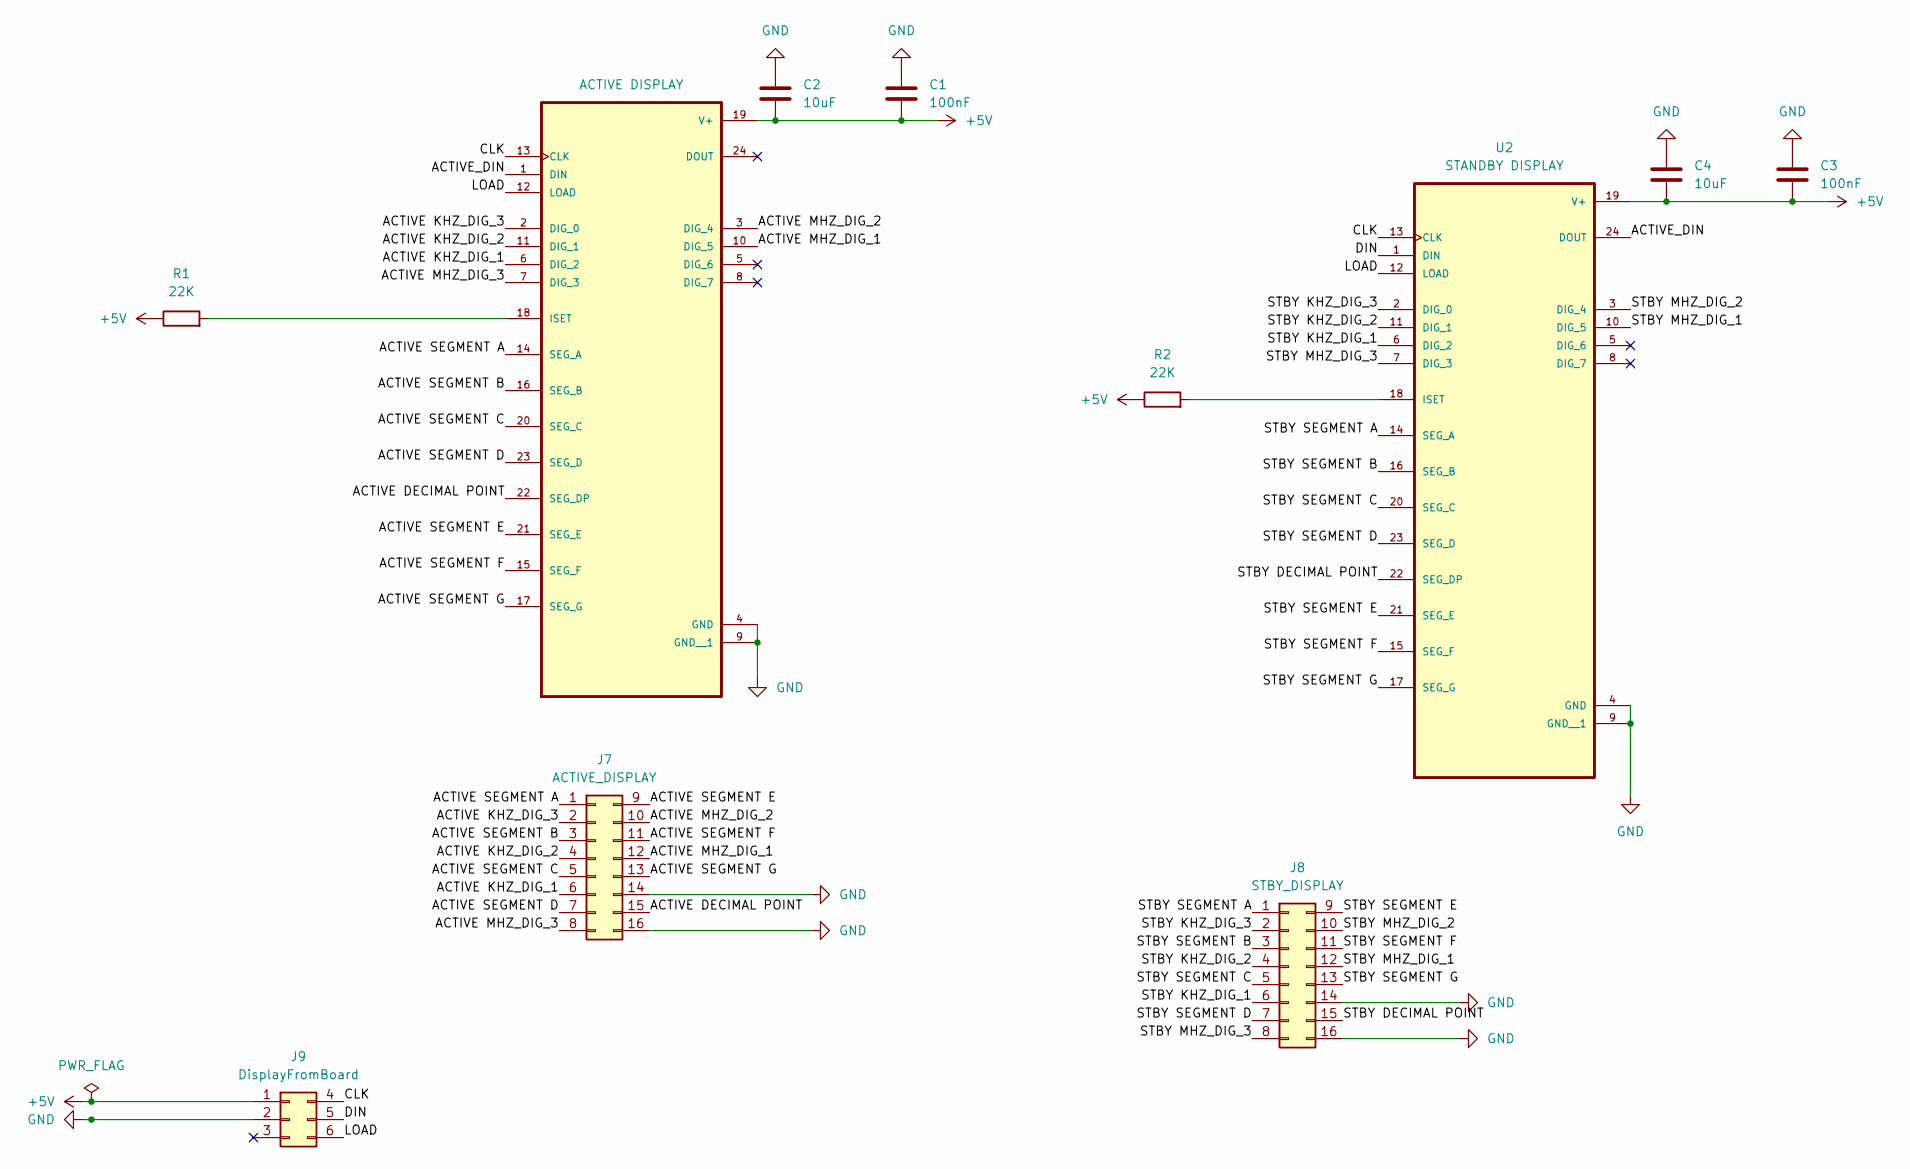
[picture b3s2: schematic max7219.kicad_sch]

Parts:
C1, C3: 100nF; C_1206_3216Metric
C2, C4: 10uF; C_1206_3216Metric
J7: ACTIVE_DISPLAY; PinHeader_2x08_P2.54mm_Vertical
J8: STBY_DISPLAY; PinHeader_2x08_P2.54mm_Vertical
J9: DisplayFromBoard; PinHeader_2x03_P2.54mm_Vertical
R1, R2: 22K; R_1206_3216Metric
U1: ACTIVE DISPLAY; SOIC127P1032X265-24N
U2: STANDBY DISPLAY; SOIC127P1032X265-24N

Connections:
+5V: C1.2, C2.2, C3.2, C4.2, J9.1, R1.1, R2.1, U1.19 (V+), U2.19 (V+)
/Max7219 Displays/ACTIVE DECIMAL POINT: J7.15, U1.22 (SEG_DP)
/Max7219 Displays/ACTIVE KHZ_DIG_1: J7.6, U1.6 (DIG_2)
/Max7219 Displays/ACTIVE KHZ_DIG_2: J7.4, U1.11 (DIG_1)
/Max7219 Displays/ACTIVE KHZ_DIG_3: J7.2, U1.2 (DIG_0)
/Max7219 Displays/ACTIVE MHZ_DIG_1: J7.12, U1.10 (DIG_5)
/Max7219 Displays/ACTIVE MHZ_DIG_2: J7.10, U1.3 (DIG_4)
/Max7219 Displays/ACTIVE MHZ_DIG_3: J7.8, U1.7 (DIG_3)
/Max7219 Displays/ACTIVE SEGMENT A: J7.1, U1.14 (SEG_A)
/Max7219 Displays/ACTIVE SEGMENT B: J7.3, U1.16 (SEG_B)
/Max7219 Displays/ACTIVE SEGMENT C: J7.5, U1.20 (SEG_C)
/Max7219 Displays/ACTIVE SEGMENT D: J7.7, U1.23 (SEG_D)
/Max7219 Displays/ACTIVE SEGMENT E: J7.9, U1.21 (SEG_E)
/Max7219 Displays/ACTIVE SEGMENT F: J7.11, U1.15 (SEG_F)
/Max7219 Displays/ACTIVE SEGMENT G: J7.13, U1.17 (SEG_G)
/Max7219 Displays/ACTIVE_DIN: U1.1 (DIN), U2.24 (DOUT)
/Max7219 Displays/CLK: J9.4, U1.13 (CLK), U2.13 (CLK)
/Max7219 Displays/DIN: J9.5, U2.1 (DIN)
/Max7219 Displays/LOAD: J9.6, U1.12 (LOAD), U2.12 (LOAD)
/Max7219 Displays/STBY DECIMAL POINT: J8.15, U2.22 (SEG_DP)
/Max7219 Displays/STBY KHZ_DIG_1: J8.6, U2.6 (DIG_2)
/Max7219 Displays/STBY KHZ_DIG_2: J8.4, U2.11 (DIG_1)
/Max7219 Displays/STBY KHZ_DIG_3: J8.2, U2.2 (DIG_0)
/Max7219 Displays/STBY MHZ_DIG_1: J8.12, U2.10 (DIG_5)
/Max7219 Displays/STBY MHZ_DIG_2: J8.10, U2.3 (DIG_4)
/Max7219 Displays/STBY MHZ_DIG_3: J8.8, U2.7 (DIG_3)
/Max7219 Displays/STBY SEGMENT A: J8.1, U2.14 (SEG_A)
/Max7219 Displays/STBY SEGMENT B: J8.3, U2.16 (SEG_B)
/Max7219 Displays/STBY SEGMENT C: J8.5, U2.20 (SEG_C)
/Max7219 Displays/STBY SEGMENT D: J8.7, U2.23 (SEG_D)
/Max7219 Displays/STBY SEGMENT E: J8.9, U2.21 (SEG_E)
/Max7219 Displays/STBY SEGMENT F: J8.11, U2.15 (SEG_F)
/Max7219 Displays/STBY SEGMENT G: J8.13, U2.17 (SEG_G)
GND: C1.1, C2.1, C3.1, C4.1, J7.14, J7.16, J8.14, J8.16, J9.2, U1.4 (GND), U1.9 (GND__1), U2.4 (GND), U2.9 (GND__1); also elsewhere on the board
unnamed: R1.2, U1.18 (ISET)
unnamed: R2.2, U2.18 (ISET)
